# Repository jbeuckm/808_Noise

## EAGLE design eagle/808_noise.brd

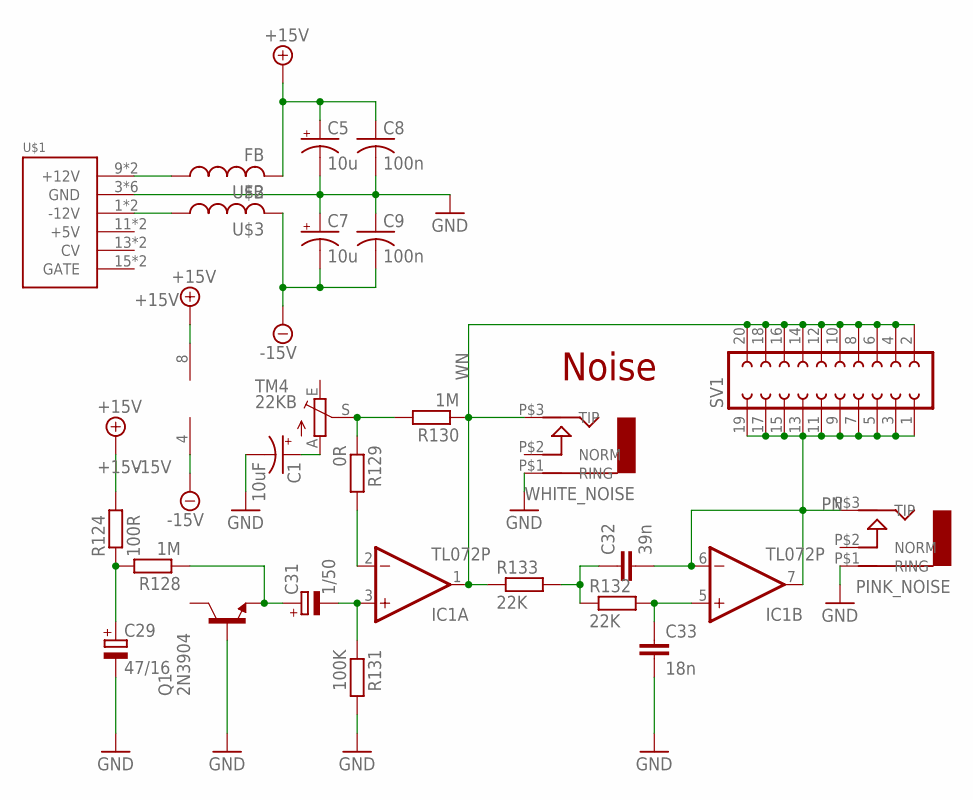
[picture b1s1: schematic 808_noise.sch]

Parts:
C1: 10uF; B45181A
C5, C7: 10u; B45181A
C8, C9: 100n; C050-024X044
C29: 47/16; E2,5-5
C31: 1/50; E2,5-5
C32: 39n; C050-024X044
C33: 18n; C035-030X60
IC1: TL072P; DIL08
PINK_NOISE: AUDIO-JACK; ERTHENVAR-JACK-90DEG
Q1: 2N3904; TO92
R124: 100R; 0207/7
R128, R130: 1M; 0207/7
R129: 0R; 0207/7
R131: 100K; 0207/7
R132, R133: 22K; 0207/7
SV1: FE10-2
TM4: 22KB; B64Y
U$1: POWER; POWER_16
U$2, U$3: FB
WHITE_NOISE: AUDIO-JACK; ERTHENVAR-JACK-90DEG

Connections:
+15V: C5.+, C8.1, IC1.8 (V+), R124.2, U$2.P$2 (2)
-15V: C7.-, C9.2, IC1.4 (V-), U$3.P$2 (2)
GND: C1.-, C5.-, C7.+, C8.2, C9.1, C29.-, C33.P$2 (2), PINK_NOISE.P$1 (RING), Q1.2 (B), R131.2, U$1.3 (GND), U$1.4 (GND), U$1.5 (GND), U$1.6 (GND), U$1.7 (GND), U$1.8 (GND), WHITE_NOISE.P$1 (RING)
unnamed: C1.+, TM4.A
unnamed: IC1.2 (-IN), R129.2
unnamed: U$1.9 (+12V), U$1.10 (+12V), U$2.P$1 (1)
unnamed: U$1.1 (-12V), U$1.2 (-12V), U$3.P$1 (1)
unnamed: C31.-, IC1.3 (+IN), R131.1
unnamed: R129.1, R130.2, TM4.S
unnamed: C31.+, Q1.3 (E), R128.1
unnamed: C29.+, R124.1, R128.2
unnamed: C32.1, R132.1, R133.2
unnamed: C33.P$1 (1), IC1.5 (+IN), R132.2
PN: C32.2, IC1.6 (-IN), IC1.7 (OUT), PINK_NOISE.P$3 (TIP), SV1.1, SV1.3, SV1.5, SV1.7, SV1.9, SV1.11, SV1.13, SV1.15, SV1.17, SV1.19
WN: IC1.1 (OUT), R130.1, R133.1, SV1.2, SV1.4, SV1.6, SV1.8, SV1.10, SV1.12, SV1.14, SV1.16, SV1.18, SV1.20, WHITE_NOISE.P$3 (TIP)

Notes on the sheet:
Noise

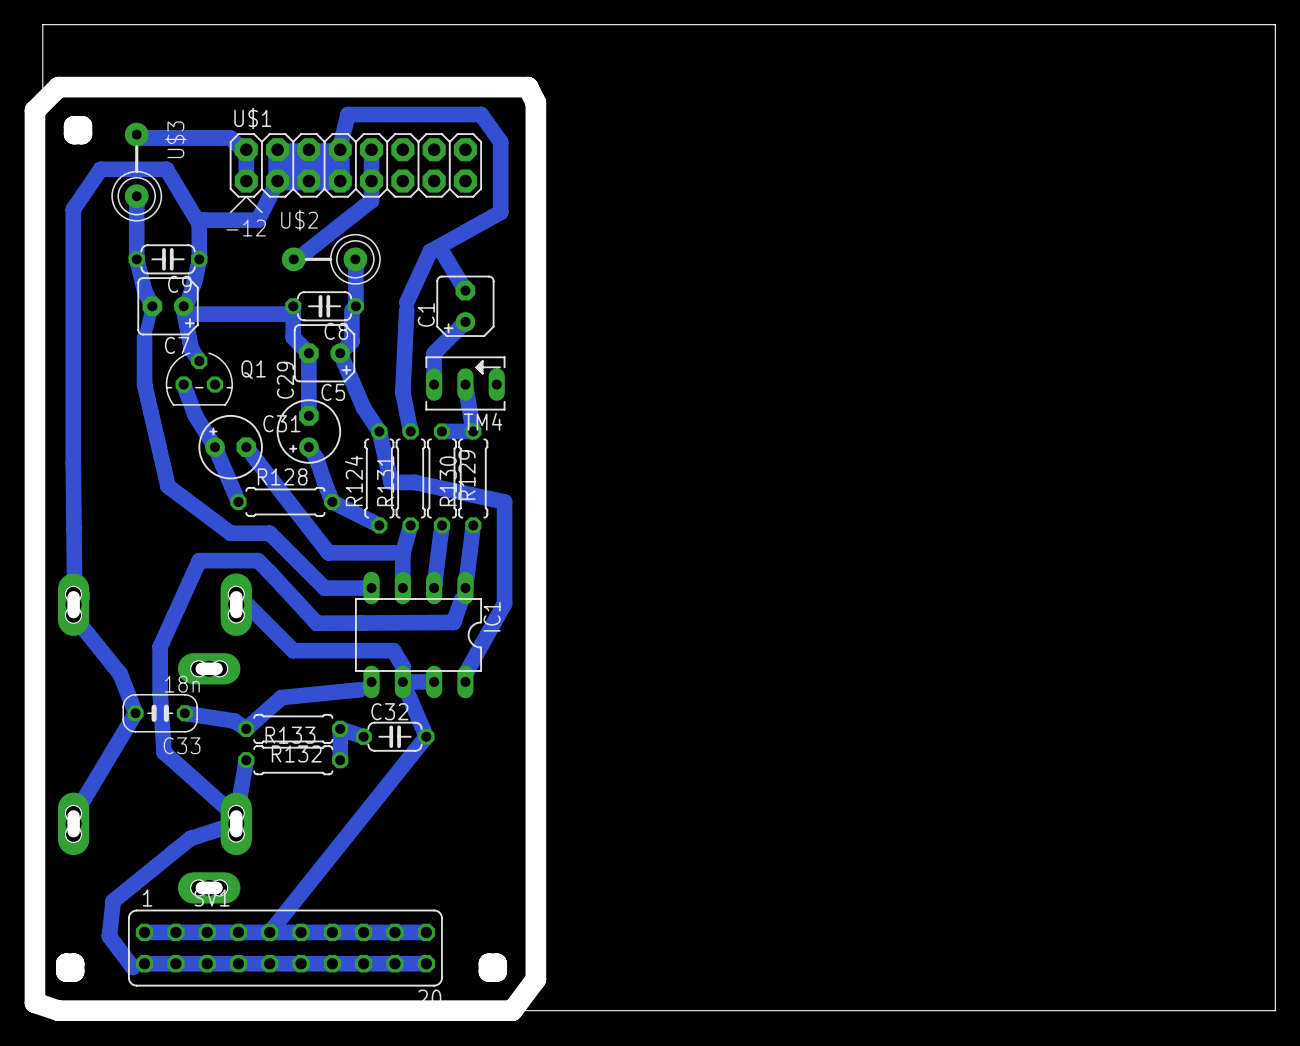
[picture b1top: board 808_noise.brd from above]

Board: 2 copper layers, 99.8 x 79.2 mm, 25 parts (0 on the bottom side), 15 nets.

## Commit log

2016-04-15 routed
2016-04-16 cutout
2016-04-16 gcode
2016-04-21 with mods
2016-05-16 svg panel
2018-06-01 tweak labels and new layout png
